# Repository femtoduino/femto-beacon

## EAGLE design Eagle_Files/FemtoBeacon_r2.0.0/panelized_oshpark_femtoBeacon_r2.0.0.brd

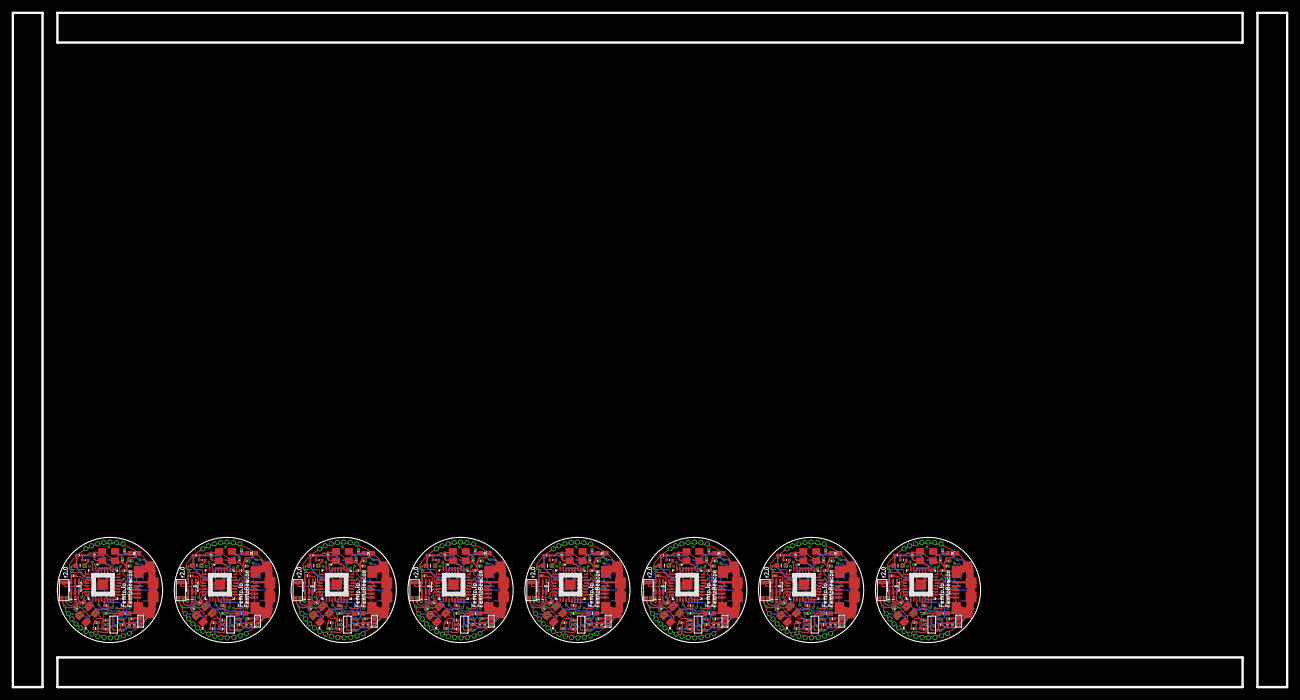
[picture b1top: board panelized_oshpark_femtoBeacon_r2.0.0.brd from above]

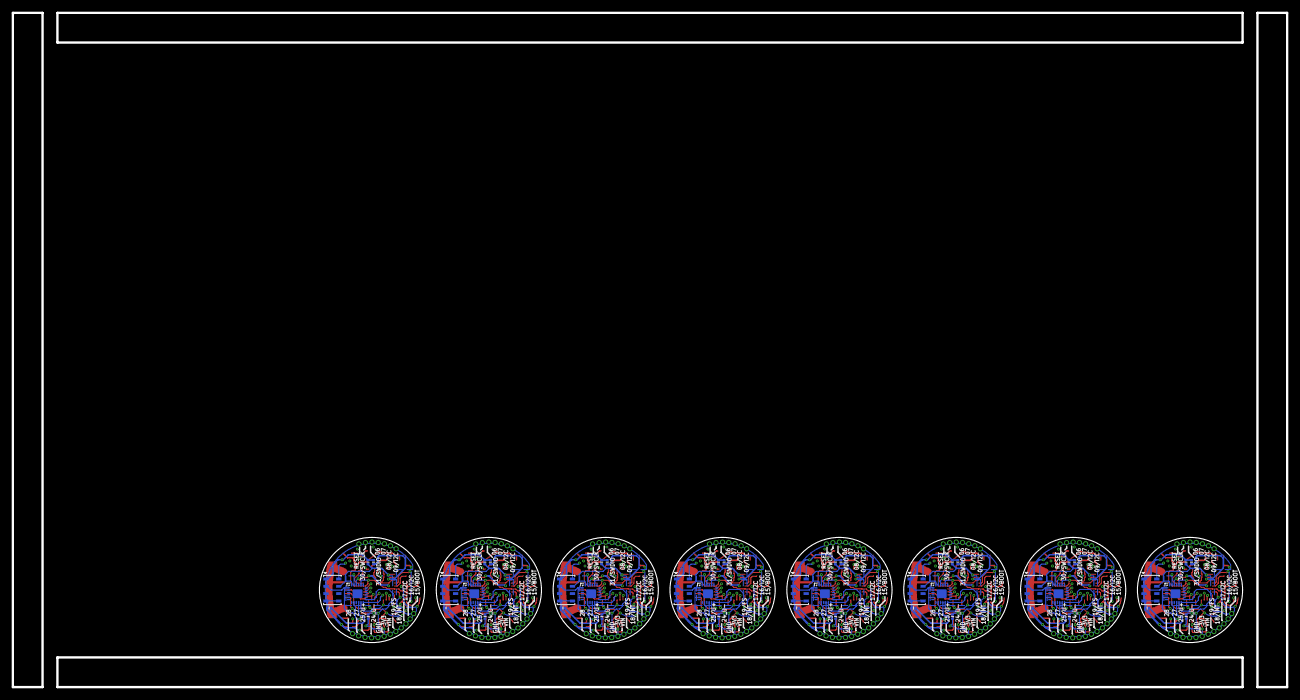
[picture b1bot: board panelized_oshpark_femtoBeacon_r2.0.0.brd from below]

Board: 4 copper layers, 218.1 x 115.4 mm, 480 parts (56 on the bottom side), 288 nets.

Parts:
ANT1, ANT2, ANT3, ANT4, ANT5, ANT6, ANT7, ANT8: PULSE_ANT_2.4GHZ; ANT_BAR
BTN, BTN1, BTN2, BTN3, BTN4, BTN5, BTN6, BTN7: DNP; SPST_SMD
C1, C2, C8, C9, C10, C16, C17, C18, C19, C25, C26, C27, C28, C29, C30, C32, C33, C36, C45, C46, C47, C48, C52, C53, C54, C55, C56, C59, C68, C69, C70, C71, C75, C76, C77, C78, C79, C82, C91, C92, C93, C94, C98, C99, C100, C101, C102, C105, C114, C115, C116, C117, C121, C122, C123, C124, C125, C128, C137, C138, C139, C140, C144, C145, C146, C147, C148, C151, C160, C161, C162, C163, C167, C168, C169, C170, C171, C174, C183, C184: 0.1uF; PART
C3, C4, C37, C38, C60, C61, C83, C84, C106, C107, C129, C130, C152, C153, C175, C176: 10pF; PART
C5, C6, C20, C23, C49, C50, C72, C73, C95, C96, C118, C119, C141, C142, C164, C165: 2.2uF; PART
C7, C24, C51, C74, C97, C120, C143, C166: 0.47uF; PART
C11, C12, C39, C40, C62, C63, C85, C86, C108, C109, C131, C132, C154, C155, C177, C178: 22pF, C0G, 5%; PART
C13, C41, C64, C87, C110, C133, C156, C179: DNP; PART
C14, C15, C42, C43, C65, C66, C88, C89, C111, C112, C134, C135, C157, C158, C180, C181: 9pF; PART
C21, C22, C34, C35, C57, C58, C80, C81, C103, C104, C126, C127, C149, C150, C172, C173: 10uF; _0402MP
C31, C44, C67, C90, C113, C136, C159, C182: 10nF; PART
FB1, FB2, FB3, FB4, FB5, FB6, FB7, FB8: _0603MP
L1, L2, L3, L4, L5, L6, L7, L8: 10uH; _0603MP
LDO_VREG, LDO_VREG1, LDO_VREG2, LDO_VREG3, LDO_VREG4, LDO_VREG5, LDO_VREG6, LDO_VREG7: MCP1700T-3302E/TT
LED1, LED2, LED3, LED4, LED5, LED6, LED7, LED8: BLUE; CHIPLED_0603_NOOUTLINE
R1, R3, R4, R6, R11, R13, R16, R18, R21, R23, R26, R28, R31, R33, R36, R38: 330; PART
R2, R5, R12, R17, R22, R27, R32, R37: 10K; PART
R7, R8, R9, R10, R14, R15, R19, R20, R24, R25, R29, R30, R34, R35, R39, R40: 2.2K; PART
SER3628CT-ND, SER3628CT-ND1, SER3628CT-ND2, SER3628CT-ND3, SER3628CT-ND4, SER3628CT-ND5, SER3628CT-ND6, SER3628CT-ND7: 16MHz; TSX-3225
TSX-3225_CRYSTAL, TSX-3225_CRYSTAL1, TSX-3225_CRYSTAL2, TSX-3225_CRYSTAL3, TSX-3225_CRYSTAL4, TSX-3225_CRYSTAL5, TSX-3225_CRYSTAL6, TSX-3225_CRYSTAL7: 48MHz; TSX-3225
U$1, U$2, U$3, U$4, U$5, U$7, U$8, U$9, U$10, U$11, U$13, U$14, U$15, U$16, U$17, U$18, U$19, U$20, U$21, U$22, U$23, U$24, U$25, U$26, U$27, U$32, U$33, U$34, U$35, U$36, U$37, U$38, U$39, U$40, U$41, U$42, U$43, U$45, U$46, U$47, U$48, U$49, U$50, U$51, U$52, U$53, U$54, U$55, U$56, U$57, U$58, U$59, U$60, U$61, U$62, U$63, U$64, U$69, U$70, U$71, U$72, U$73, U$74, U$75, U$77, U$78, U$79, U$80, U$81, U$82, U$83, U$84, U$85, U$86, U$87, U$88, U$93, U$94, U$95, U$96, U$97, U$98, U$99, U$100, U$101, U$102, U$103, U$104, U$105, U$106, U$107, U$108, U$109, U$110, U$111, U$116, U$117, U$118, U$119, U$120, U$121, U$122, U$123, U$124, U$125, U$126, U$127, U$128, U$129, U$130, U$131, U$132, U$133, U$134, U$139, U$140, U$141, U$142, U$143, U$144, U$145, U$146, U$147, U$148, U$149, U$150, U$151, U$152, U$153, U$154, U$155, U$156, U$157, U$162, U$163, U$164, U$165, U$166, U$167, U$168, U$169, U$170, U$171, U$172, U$173, U$174, U$175, U$176, U$177, U$178, U$179, U$180: 1X1_ROUND
U$6, U$31, U$68, U$92, U$115, U$138, U$161, U$184: MPU-9250; QFN_3X3MM
U$12, U$30, U$67, U$91, U$114, U$137, U$160, U$183: JOHANSON_2450BM15A0015E; 0805_BALUN
U$28, U$44, U$65, U$89, U$112, U$135, U$158, U$181: MS5611-01BA03
U$29, U$66, U$76, U$90, U$113, U$136, U$159, U$182: ATSAMR21E18A-MUT; QFN32
USB, USB1, USB2, USB3, USB4, USB5, USB6, USB7: USB_MICROB; USB_MICROB_PACKAGE

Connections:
3.3V: C5.1, C10.1, C16.1, C21.2, C29.1, C30.2, C31.2, L6.1, LDO_VREG.VOUT, R2.2, R8.2, R9.2, U$5.P$1, U$6.P$1, U$6.P$8, U$6.P$13, U$6.P$22, U$44.1, U$44.2, U$76.24, U$76.30
3.3V1: C20.1, C25.1, C28.1, C34.2, C36.1, C44.2, C45.2, L1.1, LDO_VREG1.VOUT, R5.2, R7.2, R10.2, U$8.P$1, U$28.1, U$28.2, U$29.24, U$29.30, U$31.P$1, U$31.P$8, U$31.P$13, U$31.P$22
3.3V2: C49.1, C52.1, C55.1, C57.2, C59.1, C67.2, C68.2, L2.1, LDO_VREG2.VOUT, R12.2, R14.2, R15.2, U$34.P$1, U$65.1, U$65.2, U$66.24, U$66.30, U$68.P$1, U$68.P$8, U$68.P$13, U$68.P$22
3.3V3: C72.1, C75.1, C78.1, C80.2, C82.1, C90.2, C91.2, L3.1, LDO_VREG3.VOUT, R17.2, R19.2, R20.2, U$71.P$1, U$89.1, U$89.2, U$90.24, U$90.30, U$92.P$1, U$92.P$8, U$92.P$13, U$92.P$22
3.3V4: C95.1, C98.1, C101.1, C103.2, C105.1, C113.2, C114.2, L4.1, LDO_VREG4.VOUT, R22.2, R24.2, R25.2, U$95.P$1, U$112.1, U$112.2, U$113.24, U$113.30, U$115.P$1, U$115.P$8, U$115.P$13, U$115.P$22
3.3V5: C118.1, C121.1, C124.1, C126.2, C128.1, C136.2, C137.2, L5.1, LDO_VREG5.VOUT, R27.2, R29.2, R30.2, U$118.P$1, U$135.1, U$135.2, U$136.24, U$136.30, U$138.P$1, U$138.P$8, U$138.P$13, U$138.P$22
3.3V6: C141.1, C144.1, C147.1, C149.2, C151.1, C159.2, C160.2, L7.1, LDO_VREG6.VOUT, R32.2, R34.2, R35.2, U$141.P$1, U$158.1, U$158.2, U$159.24, U$159.30, U$161.P$1, U$161.P$8, U$161.P$13, U$161.P$22
3.3V7: C164.1, C167.1, C170.1, C172.2, C174.1, C182.2, C183.2, L8.1, LDO_VREG7.VOUT, R37.2, R39.2, R40.2, U$164.P$1, U$181.1, U$181.2, U$182.24, U$182.30, U$184.P$1, U$184.P$8, U$184.P$13, U$184.P$22
ANT_OUT: ANT1.1, U$12.1
ANT_OUT1: ANT2.1, U$30.1
ANT_OUT2: ANT3.1, U$67.1
ANT_OUT3: ANT4.1, U$91.1
ANT_OUT4: ANT5.1, U$114.1
ANT_OUT5: ANT6.1, U$137.1
ANT_OUT6: ANT7.1, U$160.1
ANT_OUT7: ANT8.1, U$183.1
AVDD: C17.1, U$76.5
AVDD1: C33.1, U$29.5
AVDD2: C56.1, U$66.5
AVDD3: C79.1, U$90.5
AVDD4: C102.1, U$113.5
AVDD5: C125.1, U$136.5
AVDD6: C148.1, U$159.5
AVDD7: C171.1, U$182.5
DVDD: C2.1, U$76.21
DVDD1: C19.1, U$29.21
DVDD2: C48.1, U$66.21
DVDD3: C71.1, U$90.21
DVDD4: C94.1, U$113.21
DVDD5: C117.1, U$136.21
DVDD6: C140.1, U$159.21
DVDD7: C163.1, U$182.21
GND: ANT1.3, BTN.2, C1.2, C2.2, C3.1, C4.2, C5.2, C6.2, C7.2, C8.2, C9.2, C10.2, C13.2, C14.1, C15.2, C16.2, C17.2, C21.1, C22.1, C29.2, C30.1, C31.1, C32.2, FB1.2, LDO_VREG.GND, LED2.C, SER3628CT-ND.2, SER3628CT-ND.4, TSX-3225_CRYSTAL.2, TSX-3225_CRYSTAL.4, U$2.P$1, U$6.P$20, U$12.2, U$12.5, U$12.6, U$44.3, U$44.4, U$44.5, U$76.3, U$76.6, U$76.11, U$76.14, U$76.28, U$76.33
GND1: ANT2.3, BTN1.2, C18.2, C19.2, C20.2, C23.2, C24.2, C25.2, C26.2, C27.2, C28.2, C33.2, C34.1, C35.1, C36.2, C37.1, C38.2, C41.2, C42.1, C43.2, C44.1, C45.1, C46.2, FB2.2, LDO_VREG1.GND, LED1.C, SER3628CT-ND1.2, SER3628CT-ND1.4, TSX-3225_CRYSTAL1.2, TSX-3225_CRYSTAL1.4, U$4.P$1, U$28.3, U$28.4, U$28.5, U$29.3, U$29.6, U$29.11, U$29.14, U$29.28, U$29.33, U$30.2, U$30.5, U$30.6, U$31.P$20
GND2: ANT3.3, BTN2.2, C47.2, C48.2, C49.2, C50.2, C51.2, C52.2, C53.2, C54.2, C55.2, C56.2, C57.1, C58.1, C59.2, C60.1, C61.2, C64.2, C65.1, C66.2, C67.1, C68.1, C69.2, FB3.2, LDO_VREG2.GND, LED3.C, SER3628CT-ND2.2, SER3628CT-ND2.4, TSX-3225_CRYSTAL2.2, TSX-3225_CRYSTAL2.4, U$33.P$1, U$65.3, U$65.4, U$65.5, U$66.3, U$66.6, U$66.11, U$66.14, U$66.28, U$66.33, U$67.2, U$67.5, U$67.6, U$68.P$20
GND3: ANT4.3, BTN3.2, C70.2, C71.2, C72.2, C73.2, C74.2, C75.2, C76.2, C77.2, C78.2, C79.2, C80.1, C81.1, C82.2, C83.1, C84.2, C87.2, C88.1, C89.2, C90.1, C91.1, C92.2, FB4.2, LDO_VREG3.GND, LED4.C, SER3628CT-ND3.2, SER3628CT-ND3.4, TSX-3225_CRYSTAL3.2, TSX-3225_CRYSTAL3.4, U$70.P$1, U$89.3, U$89.4, U$89.5, U$90.3, U$90.6, U$90.11, U$90.14, U$90.28, U$90.33, U$91.2, U$91.5, U$91.6, U$92.P$20
GND4: ANT5.3, BTN4.2, C93.2, C94.2, C95.2, C96.2, C97.2, C98.2, C99.2, C100.2, C101.2, C102.2, C103.1, C104.1, C105.2, C106.1, C107.2, C110.2, C111.1, C112.2, C113.1, C114.1, C115.2, FB5.2, LDO_VREG4.GND, LED5.C, SER3628CT-ND4.2, SER3628CT-ND4.4, TSX-3225_CRYSTAL4.2, TSX-3225_CRYSTAL4.4, U$94.P$1, U$112.3, U$112.4, U$112.5, U$113.3, U$113.6, U$113.11, U$113.14, U$113.28, U$113.33, U$114.2, U$114.5, U$114.6, U$115.P$20
GND5: ANT6.3, BTN5.2, C116.2, C117.2, C118.2, C119.2, C120.2, C121.2, C122.2, C123.2, C124.2, C125.2, C126.1, C127.1, C128.2, C129.1, C130.2, C133.2, C134.1, C135.2, C136.1, C137.1, C138.2, FB6.2, LDO_VREG5.GND, LED6.C, SER3628CT-ND5.2, SER3628CT-ND5.4, TSX-3225_CRYSTAL5.2, TSX-3225_CRYSTAL5.4, U$117.P$1, U$135.3, U$135.4, U$135.5, U$136.3, U$136.6, U$136.11, U$136.14, U$136.28, U$136.33, U$137.2, U$137.5, U$137.6, U$138.P$20
GND6: ANT7.3, BTN6.2, C139.2, C140.2, C141.2, C142.2, C143.2, C144.2, C145.2, C146.2, C147.2, C148.2, C149.1, C150.1, C151.2, C152.1, C153.2, C156.2, C157.1, C158.2, C159.1, C160.1, C161.2, FB7.2, LDO_VREG6.GND, LED7.C, SER3628CT-ND6.2, SER3628CT-ND6.4, TSX-3225_CRYSTAL6.2, TSX-3225_CRYSTAL6.4, U$140.P$1, U$158.3, U$158.4, U$158.5, U$159.3, U$159.6, U$159.11, U$159.14, U$159.28, U$159.33, U$160.2, U$160.5, U$160.6, U$161.P$20
GND7: ANT8.3, BTN7.2, C162.2, C163.2, C164.2, C165.2, C166.2, C167.2, C168.2, C169.2, C170.2, C171.2, C172.1, C173.1, C174.2, C175.1, C176.2, C179.2, C180.1, C181.2, C182.1, C183.1, C184.2, FB8.2, LDO_VREG7.GND, LED8.C, SER3628CT-ND7.2, SER3628CT-ND7.4, TSX-3225_CRYSTAL7.2, TSX-3225_CRYSTAL7.4, U$163.P$1, U$181.3, U$181.4, U$181.5, U$182.3, U$182.6, U$182.11, U$182.14, U$182.28, U$182.33, U$183.2, U$183.5, U$183.6, U$184.P$20
unnamed: C11.2, U$12.3
unnamed: ANT1.2, C13.1
unnamed: C12.2, U$12.4
unnamed: C32.1, U$6.P$10
unnamed: FB1.1, USB.5, USB.6, USB.7, USB.8, USB.9, USB.10, USB.11
unnamed: BTN1.1, R3.1
unnamed: LED1.A, R6.2
unnamed: C39.2, U$30.3
unnamed: C40.2, U$30.4
unnamed: ANT2.2, C41.1
unnamed: C46.1, U$31.P$10
unnamed: LED2.A, R4.2
unnamed: FB2.1, USB1.5, USB1.6, USB1.7, USB1.8, USB1.9, USB1.10, USB1.11
unnamed: BTN2.1, R11.1
unnamed: LED3.A, R13.2
unnamed: C62.2, U$67.3
unnamed: C63.2, U$67.4
unnamed: ANT3.2, C64.1
unnamed: C69.1, U$68.P$10
unnamed: FB3.1, USB2.5, USB2.6, USB2.7, USB2.8, USB2.9, USB2.10, USB2.11
unnamed: BTN3.1, R16.1
unnamed: LED4.A, R18.2
unnamed: BTN.1, R1.1
unnamed: C85.2, U$91.3
unnamed: C86.2, U$91.4
unnamed: ANT4.2, C87.1
unnamed: C92.1, U$92.P$10
unnamed: FB4.1, USB3.5, USB3.6, USB3.7, USB3.8, USB3.9, USB3.10, USB3.11
unnamed: BTN4.1, R21.1
unnamed: LED5.A, R23.2
unnamed: C108.2, U$114.3
unnamed: C109.2, U$114.4
unnamed: ANT5.2, C110.1
unnamed: C115.1, U$115.P$10
unnamed: FB5.1, USB4.5, USB4.6, USB4.7, USB4.8, USB4.9, USB4.10, USB4.11
unnamed: BTN5.1, R26.1
unnamed: LED6.A, R28.2
unnamed: C131.2, U$137.3
unnamed: C132.2, U$137.4
unnamed: ANT6.2, C133.1
unnamed: C138.1, U$138.P$10
unnamed: FB6.1, USB5.5, USB5.6, USB5.7, USB5.8, USB5.9, USB5.10, USB5.11
unnamed: BTN6.1, R31.1
unnamed: LED7.A, R33.2
unnamed: C154.2, U$160.3
unnamed: C155.2, U$160.4
unnamed: ANT7.2, C156.1
unnamed: C161.1, U$161.P$10
unnamed: FB7.1, USB6.5, USB6.6, USB6.7, USB6.8, USB6.9, USB6.10, USB6.11
unnamed: BTN7.1, R36.1
unnamed: LED8.A, R38.2
unnamed: C177.2, U$183.3
unnamed: C178.2, U$183.4
unnamed: ANT8.2, C179.1
unnamed: C184.1, U$184.P$10
unnamed: FB8.1, USB7.5, USB7.6, USB7.7, USB7.8, USB7.9, USB7.10, USB7.11
PA01: U$25.P$1, U$29.7
PA02: U$19.P$1, U$29.8
PA03: U$23.P$1, U$29.25
PA04: U$24.P$1, U$29.27
PA05: U$62.P$1, U$66.7
PA06: U$54.P$1, U$76.7
PA07: U$43.P$1, U$76.8
PA08: U$56.P$1, U$66.8
PA08/I2C: R8.1, U$6.P$24, U$42.P$1, U$44.7, U$76.9
PA08/I2C1: R7.1, U$18.P$1, U$28.7, U$29.9, U$31.P$24
PA08/I2C2: R14.1, U$55.P$1, U$65.7, U$66.9, U$68.P$24
PA08/I2C3: R19.1, U$79.P$1, U$89.7, U$90.9, U$92.P$24
PA08/I2C4: R24.1, U$102.P$1, U$112.7, U$113.9, U$115.P$24
PA08/I2C5: R29.1, U$125.P$1, U$135.7, U$136.9, U$138.P$24
PA08/I2C6: R34.1, U$148.P$1, U$158.7, U$159.9, U$161.P$24
PA08/I2C7: R39.1, U$171.P$1, U$181.7, U$182.9, U$184.P$24
PA09: U$60.P$1, U$66.25
PA09/I2C: R9.1, U$6.P$23, U$41.P$1, U$44.8, U$76.10
PA09/I2C1: R10.1, U$17.P$1, U$28.8, U$29.10, U$31.P$23
PA09/I2C2: R15.1, U$53.P$1, U$65.8, U$66.10, U$68.P$23
PA09/I2C3: R20.1, U$78.P$1, U$89.8, U$90.10, U$92.P$23
PA09/I2C4: R25.1, U$101.P$1, U$112.8, U$113.10, U$115.P$23
PA09/I2C5: R30.1, U$124.P$1, U$135.8, U$136.10, U$138.P$23
PA09/I2C6: R35.1, U$147.P$1, U$158.8, U$159.10, U$161.P$23
PA09/I2C7: R40.1, U$170.P$1, U$181.8, U$182.10, U$184.P$23
PA10: U$61.P$1, U$66.27
PA11: U$86.P$1, U$90.7
PA12: U$80.P$1, U$90.8
PA13: U$84.P$1, U$90.25
PA14: U$85.P$1, U$90.27
PA14/XIN_MC: C3.2, TSX-3225_CRYSTAL.1, U$76.15
PA14/XIN_MC1: C37.2, TSX-3225_CRYSTAL1.1, U$29.15
PA14/XIN_MC2: C60.2, TSX-3225_CRYSTAL2.1, U$66.15
PA14/XIN_MC3: C83.2, TSX-3225_CRYSTAL3.1, U$90.15
PA14/XIN_MC4: C106.2, TSX-3225_CRYSTAL4.1, U$113.15
PA14/XIN_MC5: C129.2, TSX-3225_CRYSTAL5.1, U$136.15
PA14/XIN_MC6: C152.2, TSX-3225_CRYSTAL6.1, U$159.15
PA14/XIN_MC7: C175.2, TSX-3225_CRYSTAL7.1, U$182.15
PA15: U$109.P$1, U$113.7
PA15/XOUT_MC: C4.1, TSX-3225_CRYSTAL.3, U$39.P$1, U$76.16
PA15/XOUT_MC1: C38.1, TSX-3225_CRYSTAL1.3, U$16.P$1, U$29.16
PA15/XOUT_MC2: C61.1, TSX-3225_CRYSTAL2.3, U$52.P$1, U$66.16
PA15/XOUT_MC3: C84.1, TSX-3225_CRYSTAL3.3, U$77.P$1, U$90.16
PA15/XOUT_MC4: C107.1, TSX-3225_CRYSTAL4.3, U$100.P$1, U$113.16
PA15/XOUT_MC5: C130.1, TSX-3225_CRYSTAL5.3, U$123.P$1, U$136.16
PA15/XOUT_MC6: C153.1, TSX-3225_CRYSTAL6.3, U$146.P$1, U$159.16
PA15/XOUT_MC7: C176.1, TSX-3225_CRYSTAL7.3, U$169.P$1, U$182.16
PA16: U$103.P$1, U$113.8
PA16/I2C: U$38.P$1, U$76.17
PA16/I2C1: U$15.P$1, U$29.17
PA16/I2C2: U$51.P$1, U$66.17
PA16/I2C3: U$75.P$1, U$90.17
PA16/I2C4: U$99.P$1, U$113.17
PA16/I2C5: U$122.P$1, U$136.17
PA16/I2C6: U$145.P$1, U$159.17
PA16/I2C7: U$168.P$1, U$182.17
PA17: U$107.P$1, U$113.25
PA17/I2C: U$37.P$1, U$76.18
PA17/I2C1: U$14.P$1, U$29.18
PA17/I2C2: U$50.P$1, U$66.18
PA17/I2C3: U$74.P$1, U$90.18
PA17/I2C4: U$98.P$1, U$113.18
PA17/I2C5: U$121.P$1, U$136.18
PA17/I2C6: U$144.P$1, U$159.18
PA17/I2C7: U$167.P$1, U$182.18
PA18: U$108.P$1, U$113.27
PA18/INTA: U$6.P$11, U$36.P$1, U$76.19
PA18/INTA1: U$13.P$1, U$29.19, U$31.P$11
PA18/INTA2: U$49.P$1, U$66.19, U$68.P$11
PA18/INTA3: U$73.P$1, U$90.19, U$92.P$11
PA18/INTA4: U$97.P$1, U$113.19, U$115.P$11
PA18/INTA5: U$120.P$1, U$136.19, U$138.P$11
PA18/INTA6: U$143.P$1, U$159.19, U$161.P$11
PA18/INTA7: U$166.P$1, U$182.19, U$184.P$11
PA19: U$132.P$1, U$136.7
PA19/FSYNC: U$6.P$12, U$35.P$1, U$76.20
PA19/FSYNC1: U$11.P$1, U$29.20, U$31.P$12
PA19/FSYNC2: U$40.P$1, U$66.20, U$68.P$12
PA19/FSYNC3: U$72.P$1, U$90.20, U$92.P$12
PA19/FSYNC4: U$96.P$1, U$113.20, U$115.P$12
PA19/FSYNC5: U$119.P$1, U$136.20, U$138.P$12
PA19/FSYNC6: U$142.P$1, U$159.20, U$161.P$12
PA19/FSYNC7: U$165.P$1, U$182.20, U$184.P$12
PA20: U$126.P$1, U$136.8
PA21: U$130.P$1, U$136.25
PA22: U$131.P$1, U$136.27
PA23: U$155.P$1, U$159.7
PA24: U$149.P$1, U$159.8
PA24/USBDM: U$9.P$1, U$76.22, USB.2
PA24/USBDM1: U$26.P$1, U$29.22, USB1.2
PA24/USBDM2: U$63.P$1, U$66.22, USB2.2
PA24/USBDM3: U$87.P$1, U$90.22, USB3.2
PA24/USBDM4: U$110.P$1, U$113.22, USB4.2
PA24/USBDM5: U$133.P$1, U$136.22, USB5.2
PA24/USBDM6: U$156.P$1, U$159.22, USB6.2
PA24/USBDM7: U$179.P$1, U$182.22, USB7.2
PA25: U$153.P$1, U$159.25
PA25/USBDP: U$10.P$1, U$76.23, USB.3
PA25/USBDP1: U$27.P$1, U$29.23, USB1.3
PA25/USBDP2: U$64.P$1, U$66.23, USB2.3
PA25/USBDP3: U$88.P$1, U$90.23, USB3.3
PA25/USBDP4: U$111.P$1, U$113.23, USB4.3
PA25/USBDP5: U$134.P$1, U$136.23, USB5.3
PA25/USBDP6: U$157.P$1, U$159.23, USB6.3
PA25/USBDP7: U$180.P$1, U$182.23, USB7.3
PA26: U$154.P$1, U$159.27
PA27: U$7.P$1, U$76.25
PA28: U$48.P$1, U$76.27
PA29: U$178.P$1, U$182.7
PA30: U$172.P$1, U$182.8
PA30/SWCLK: R4.1, U$46.P$1, U$76.31
PA30/SWCLK1: R6.1, U$21.P$1, U$29.31
PA30/SWCLK2: R13.1, U$58.P$1, U$66.31
PA30/SWCLK3: R18.1, U$82.P$1, U$90.31
PA30/SWCLK4: R23.1, U$105.P$1, U$113.31
PA30/SWCLK5: R28.1, U$128.P$1, U$136.31
PA30/SWCLK6: R33.1, U$151.P$1, U$159.31
PA30/SWCLK7: R38.1, U$174.P$1, U$182.31
PA31: U$176.P$1, U$182.25
PA31/SWDIO: U$47.P$1, U$76.32
PA31/SWDIO1: U$22.P$1, U$29.32
PA31/SWDIO2: U$59.P$1, U$66.32
PA31/SWDIO3: U$83.P$1, U$90.32
PA31/SWDIO4: U$106.P$1, U$113.32
PA31/SWDIO5: U$129.P$1, U$136.32
PA31/SWDIO6: U$152.P$1, U$159.32
PA31/SWDIO7: U$175.P$1, U$182.32
PA32: U$177.P$1, U$182.27
RESET: C1.1, R1.2, R2.1, U$45.P$1, U$76.26
RESET1: C18.1, R3.2, R5.1, U$20.P$1, U$29.26
RESET2: C47.1, R11.2, R12.1, U$57.P$1, U$66.26
RESET3: C70.1, R16.2, R17.1, U$81.P$1, U$90.26
RESET4: C93.1, R21.2, R22.1, U$104.P$1, U$113.26
RESET5: C116.1, R26.2, R27.1, U$127.P$1, U$136.26
RESET6: C139.1, R31.2, R32.1, U$150.P$1, U$159.26
RESET7: C162.1, R36.2, R37.1, U$173.P$1, U$182.26
RFN: C11.1, U$76.13
RFN1: C39.1, U$29.13
RFN2: C62.1, U$66.13
RFN3: C85.1, U$90.13
RFN4: C108.1, U$113.13
RFN5: C131.1, U$136.13
RFN6: C154.1, U$159.13
RFN7: C177.1, U$182.13
RFP: C12.1, U$76.12
RFP1: C40.1, U$29.12
RFP2: C63.1, U$66.12
RFP3: C86.1, U$90.12
RFP4: C109.1, U$113.12
RFP5: C132.1, U$136.12
RFP6: C155.1, U$159.12
RFP7: C178.1, U$182.12
VDDANA: C8.1, C22.2, L6.2, U$76.4
VDDANA1: C26.1, C35.2, L1.2, U$29.4
VDDANA2: C53.1, C58.2, L2.2, U$66.4
VDDANA3: C76.1, C81.2, L3.2, U$90.4
VDDANA4: C99.1, C104.2, L4.2, U$113.4
VDDANA5: C122.1, C127.2, L5.2, U$136.4
VDDANA6: C145.1, C150.2, L7.2, U$159.4
VDDANA7: C168.1, C173.2, L8.2, U$182.4
VDDCORE: C9.1, U$76.29
VDDCORE1: C27.1, U$29.29
VDDCORE2: C54.1, U$66.29
VDDCORE3: C77.1, U$90.29
VDDCORE4: C100.1, U$113.29
VDDCORE5: C123.1, U$136.29
VDDCORE6: C146.1, U$159.29
VDDCORE7: C169.1, U$182.29
VIN: C6.1, C7.1, LDO_VREG.VIN, U$1.P$1, USB.1
VIN1: C23.1, C24.1, LDO_VREG1.VIN, U$3.P$1, USB1.1
VIN2: C50.1, C51.1, LDO_VREG2.VIN, U$32.P$1, USB2.1
VIN3: C73.1, C74.1, LDO_VREG3.VIN, U$69.P$1, USB3.1
VIN4: C96.1, C97.1, LDO_VREG4.VIN, U$93.P$1, USB4.1
VIN5: C119.1, C120.1, LDO_VREG5.VIN, U$116.P$1, USB5.1
VIN6: C142.1, C143.1, LDO_VREG6.VIN, U$139.P$1, USB6.1
VIN7: C165.1, C166.1, LDO_VREG7.VIN, U$162.P$1, USB7.1
XTALIN: C14.2, SER3628CT-ND.1, U$76.2
XTALIN1: C42.2, SER3628CT-ND1.1, U$29.2
XTALIN2: C65.2, SER3628CT-ND2.1, U$66.2
XTALIN3: C88.2, SER3628CT-ND3.1, U$90.2
XTALIN4: C111.2, SER3628CT-ND4.1, U$113.2
XTALIN5: C134.2, SER3628CT-ND5.1, U$136.2
XTALIN6: C157.2, SER3628CT-ND6.1, U$159.2
XTALIN7: C180.2, SER3628CT-ND7.1, U$182.2
XTALOUT: C15.1, SER3628CT-ND.3, U$76.1
XTALOUT1: C43.1, SER3628CT-ND1.3, U$29.1
XTALOUT2: C66.1, SER3628CT-ND2.3, U$66.1
XTALOUT3: C89.1, SER3628CT-ND3.3, U$90.1
XTALOUT4: C112.1, SER3628CT-ND4.3, U$113.1
XTALOUT5: C135.1, SER3628CT-ND5.3, U$136.1
XTALOUT6: C158.1, SER3628CT-ND6.3, U$159.1
XTALOUT7: C181.1, SER3628CT-ND7.3, U$182.1

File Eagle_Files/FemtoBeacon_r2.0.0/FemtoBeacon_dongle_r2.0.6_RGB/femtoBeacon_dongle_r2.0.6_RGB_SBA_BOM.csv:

##########################################################################
       Name: Placement Bill of Materials Generator

    Version: 4 (2-sided, top)
         By: Small Batch Assembly
        URL: www.smallbatchassembly.com
 SourceFile: femtoBeacon_dongle_r2.0.6_RGB.brd
   DateTime: 1/3/18 4:22 AM
      Units: inches
##########################################################################
REF,PACKAGE,VALUE,X,Y,ROTATION,
ASWITCH   , AS222-92LF            , AS222-92LF     , 1.1500, 0.5100, 0.0
BTN   , SPST_SMD            , DNP     , 0.4800, 0.2300, 0.0
C1   , PART            , 0.1uF     , 0.5100, 0.2700, 0.0
C2   , PART            , 0.1uF     , 0.7700, 0.6900, 180.0
C5   , _0402MP            , 2.2uF     , 0.7100, 0.8300, 180.0
C6   , _0402MP            , 2.2uF     , 0.7100, 0.7400, 0.0
C7   , PART            , 0.47uF     , 0.7000, 0.7000, 0.0
C8   , PART            , 0.1uF     , 0.9000, 0.2800, 90.0
C9   , PART            , 0.1uF     , 0.6500, 0.5200, 90.0
C10   , PART            , 0.1uF     , 0.7000, 0.6500, 180.0
C11   , _0402MP            , 1.2pF     , 1.2300, 0.6000, 180.0
C13   , PART            , DNP     , 1.1100, 0.6600, 180.0
C14   , PART            , 9pF     , 0.7200, 0.2500, 270.0
C15   , PART            , 9pF     , 0.7200, 0.3100, 270.0
C16   , PART            , 0.1uF     , 0.6500, 0.4600, 270.0
C17   , PART            , 0.1uF     , 0.8300, 0.3500, 0.0
C18   , PART            , 22pF     , 1.1500, 0.5900, 270.0
C19   , PART            , 22pF     , 1.1800, 0.5900, 270.0
C20   , PART            , 22pF     , 1.1200, 0.5900, 90.0
C21   , _0402MP            , 10uF     , 0.5300, 0.7700, 270.0
C22   , _0402MP            , 10uF     , 0.8600, 0.2800, 270.0
C23   , PART            , 22pF     , 1.1760, 0.3980, 90.0
C24   , PART            , 22pF     , 1.2400, 0.5400, 90.0
CN1   , USB_A-SMT            ,      , 0.4800, 0.5300, 90.0
FB1   , _0603MP            ,      , 0.4800, 0.7700, 90.0
FB2   , _0603MP            ,      , 0.6100, 0.6900, 0.0
FID1   , FIDUCIAL_1MM            , FIDUCIAL     , 0.1000, 0.3000, 0.0
FID2   , FIDUCIAL_1MM            , FIDUCIAL     , 0.1000, 0.8000, 0.0
FID3   , FIDUCIAL_1MM            , FIDUCIAL     , 1.4500, 0.8000, 0.0
L1   , _0603MP            , 1.8nH     , 1.2060, 0.6560, 0.0
L6   , _0603MP            , 10uH     , 0.8100, 0.2800, 90.0
LDO_VREG   , MCP1700T-3302E/TT            , MCP1700T-3302E/TT     , 0.6300, 0.7800, 270.0
R1   , PART            , 330     , 0.4800, 0.3100, 0.0
R2   , PART            , 10K     , 0.5100, 0.3500, 0.0
R4   , PART            , 330     , 0.9700, 0.2600, 0.0
R6   , PART            , 330     , 0.9700, 0.3000, 0.0
R7   , PART            , 330     , 0.9800, 0.3480, 0.0
RGBLED   , LRTB_R48G            , LRTB_R48G     , 1.0300, 0.2800, 270.0
U$6   , 0479480001            , 0479480001     , 1.2040, 0.7770, 90.0
U$12   , 0805_BALUN            , JOHANSON_2450BM15A0015E     , 1.0500, 0.5100, 270.0
U$76   , QFN32            , ATSAMR21E18A-MUT     , 0.8100, 0.5100, 90.0
UFLANT   , U.FL            , uFL     , 1.1860, 0.2900, 90.0
XOSCRF   , TSX-3225            , 16MHz     , 0.6200, 0.2800, 0.0

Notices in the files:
parts and their libraries:
microbuilder: This work is placed in the public domain, and may be freely used for commercial and non-commercial work with the following conditions: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
